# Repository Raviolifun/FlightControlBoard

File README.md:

# FlightControlBoard
A PCB capable of controlling motor controllers and running a stabilizing controller.

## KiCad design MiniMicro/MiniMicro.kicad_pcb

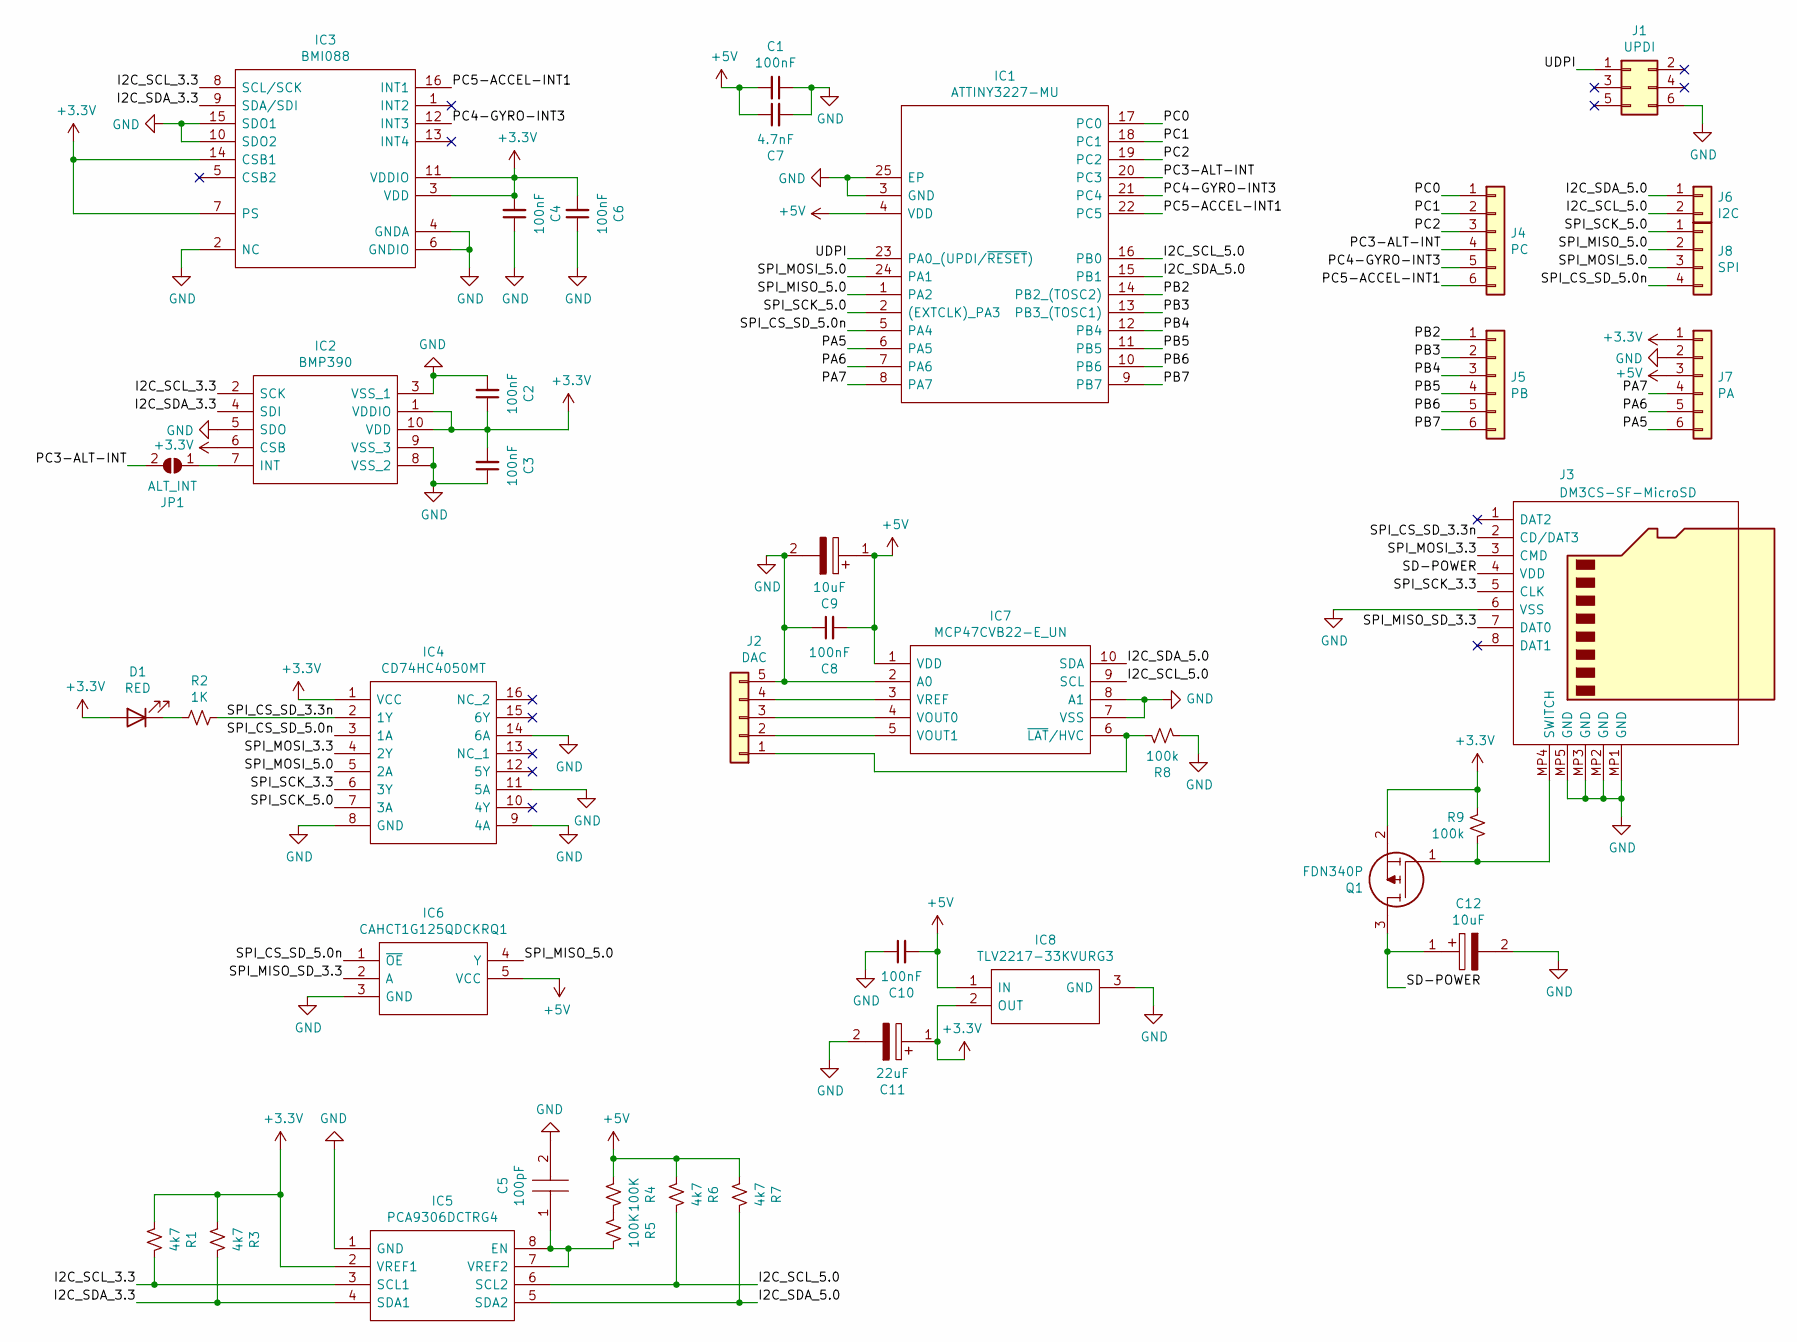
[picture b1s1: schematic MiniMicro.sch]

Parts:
C1, C2, C3, C4, C6, C8, C10: 100nF; CAPC1608X90N
C5: 100pF; CAPC1608X90N; Mouser Part Number 581-06035A101J
C7: 4.7nF; CAPC1608X90N
C9, C12: 10uF; CAPPM3216X180N; Mouser Part Number 581-TAJA106K010
C11: 22uF; CAPPM3216X180N; Mouser Part Number 74-TR3A226K010C1000
D1: RED; MHT192URCT
IC1: ATTINY3227-MU; QFN50P400X400X90-25N-D; Mouser Part Number 579-ATTINY3227-MU
IC2: BMP390; Mouser Part Number 262-BMP390
IC3: BMI088; Mouser Part Number 262-BMI088
IC4: CD74HC4050MT; SOIC127P600X175-16N; Mouser Part Number 595-CD74HC4050MT
IC5: PCA9306DCTRG4; SOP65P400X130-8N; Mouser Part Number 595-PCA9306DCTRG4
IC6: CAHCT1G125QDCKRQ1; SOT65P210X110-5N; Mouser Part Number 595-CAHCT1G125QDCKRQ
IC7: MCP47CVB22-E_UN; SOP50P490X110-10N; Mouser Part Number 579-MCP47CVB22-E/UN
IC8: TLV2217-33KVURG3; KVU0003A; Mouser Part Number 595-TLV2217-33KVURG3
J1: UPDI; PinHeader_2x03_P2.54mm_Vertical
J2: DAC; PinHeader_1x05_P2.54mm_Vertical
J3: DM3CS-SF-MicroSD; DM3CSSF; Mouser Part Number 798-DM3CSSF
J4: PC; PinHeader_1x06_P2.54mm_Vertical
J5: PB; PinHeader_1x06_P2.54mm_Vertical
J6: I2C; PinHeader_1x02_P2.54mm_Vertical
J7: PA; PinHeader_1x06_P2.54mm_Vertical
J8: SPI; PinHeader_1x04_P2.54mm_Vertical
JP1: ALT_INT; SolderJumper-2_P1.3mm_Open_RoundedPad1.0x1.5mm
Q1: FDN340P; SOT95P237X112-3N; Mouser Part Number 512-FDN340P
R1, R3, R6, R7: 4k7; 0603WAF-UNI-ROYAL
R2: 1K; 0603WAF-UNI-ROYAL
R4, R5: 100K; 0603WAF-UNI-ROYAL
R8, R9: 100k; 0603WAF-UNI-ROYAL

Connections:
+3V3: C2.1, C3.2, C4.2, C6.2, C11.1, D1.2 (A), IC2.1 (VDDIO), IC2.6 (CSB), IC2.10 (VDD), IC3.3 (VDD), IC3.7 (PS), IC3.11 (VDDIO), IC3.14 (CSB1), IC4.1 (VCC), IC5.2 (VREF1), IC8.2 (OUT), J7.1, Q1.2, R1.1, R3.1, R9.1
+5V: C1.2, C7.1, C8.2, C9.1, C10.2, IC1.4 (VDD), IC6.5 (VCC), IC7.1 (VDD), IC8.1 (IN), J7.3, R4.1, R6.1, R7.1
/I2C_SCL_3.3: IC2.2 (SCK), IC3.8 (SCL/SCK), IC5.3 (SCL1), R1.2
/I2C_SCL_5.0: IC1.16 (PB0), IC5.6 (SCL2), IC7.9 (SCL), J6.2, R6.2
/I2C_SDA_3.3: IC2.4 (SDI), IC3.9 (SDA/SDI), IC5.4 (SDA1), R3.2
/I2C_SDA_5.0: IC1.15 (PB1), IC5.5 (SDA2), IC7.10 (SDA), J6.1, R7.2
/PA5: IC1.6 (PA5), J7.6
/PA6: IC1.7 (PA6), J7.5
/PA7: IC1.8 (PA7), J7.4
/PB2: IC1.14 (PB2_(TOSC2)), J5.1
/PB3: IC1.13 (PB3_(TOSC1)), J5.2
/PB4: IC1.12 (PB4), J5.3
/PB5: IC1.11 (PB5), J5.4
/PB6: IC1.10 (PB6), J5.5
/PB7: IC1.9 (PB7), J5.6
/PC0: IC1.17 (PC0), J4.1
/PC1: IC1.18 (PC1), J4.2
/PC2: IC1.19 (PC2), J4.3
/PC3-ALT-INT: IC1.20 (PC3), J4.4, JP1.2 (B)
/PC4-GYRO-INT3: IC1.21 (PC4), IC3.12 (INT3), J4.5
/PC5-ACCEL-INT1: IC1.22 (PC5), IC3.16 (INT1), J4.6
/SD-POWER: C12.1, J3.4 (VDD), Q1.3
/SPI_CS_SD_3.3n: IC4.2 (1Y), J3.2 (CD/DAT3), R2.1
/SPI_CS_SD_5.0n: IC1.5 (PA4), IC4.3 (1A), IC6.1 (~OE), J8.4
/SPI_MISO_5.0: IC1.1 (PA2), IC6.4 (Y), J8.2
/SPI_MISO_SD_3.3: IC6.2 (A), J3.7 (DAT0)
/SPI_MOSI_3.3: IC4.4 (2Y), J3.3 (CMD)
/SPI_MOSI_5.0: IC1.24 (PA1), IC4.5 (2A), J8.3
/SPI_SCK_3.3: IC4.6 (3Y), J3.5 (CLK)
/SPI_SCK_5.0: IC1.2 ((EXTCLK)_PA3), IC4.7 (3A), J8.1
/UDPI: IC1.23 (PA0_(UPDI/~RESET)), J1.1
GND: C1.1, C2.2, C3.1, C4.1, C5.2, C6.1, C7.2, C8.1, C9.2, C10.1, C11.2, C12.2, IC1.3 (GND), IC1.25 (EP), IC2.3 (VSS_1), IC2.5 (SDO), IC2.8 (VSS_2), IC2.9 (VSS_3), IC3.2 (NC), IC3.4 (GNDA), IC3.6 (GNDIO), IC3.10 (SDO2), IC3.15 (SDO1), IC4.8 (GND), IC4.9 (4A), IC4.11 (5A), IC4.14 (6A), IC5.1 (GND), IC6.3 (GND), IC7.2 (A0), IC7.7 (VSS), IC7.8 (A1), IC8.3 (GND), J1.6, J2.5, J3.6 (VSS), J3.MP1 (GND), J3.MP2 (GND), J3.MP3 (GND), J3.MP5 (GND), J7.2, R8.1
unnamed: C5.1, IC5.7 (VREF2), IC5.8 (EN), R5.2
unnamed: D1.1 (K), R2.2
unnamed: IC2.7 (INT), JP1.1 (A)
unnamed: IC7.3 (VREF), J2.4
unnamed: IC7.4 (VOUT0), J2.3
unnamed: IC7.5 (VOUT1), J2.2
unnamed: IC7.6 (~LAT~/HVC), J2.1, R8.2
unnamed: J3.MP4 (SWITCH), Q1.1, R9.2
unnamed: R4.2, R5.1

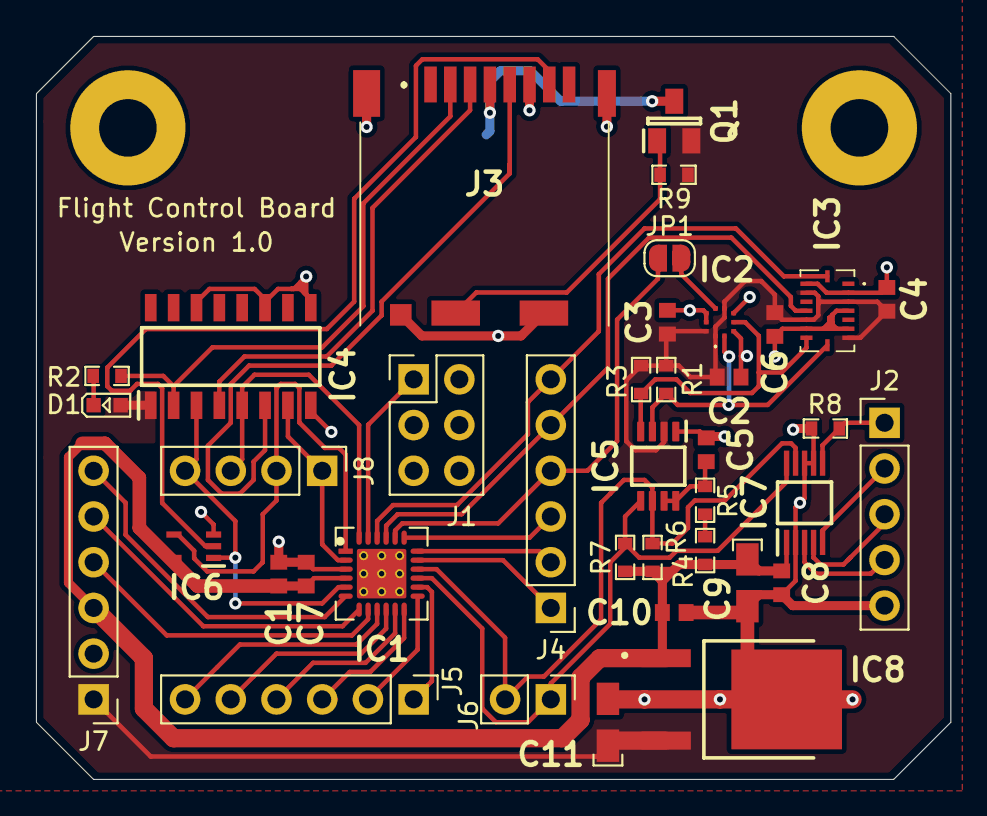
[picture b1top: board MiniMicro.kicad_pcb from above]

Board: 2 copper layers, 50.8 x 41.3 mm, 40 parts (1 on the bottom side), 41 nets.

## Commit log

2022-09-01 Initial PCB Commit
